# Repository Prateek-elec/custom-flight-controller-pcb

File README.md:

# Custom Drone Flight Controller PCB (KiCad)

A custom-designed drone flight controller PCB built for UAV / robotics applications.
This repository contains schematic + PCB layout designed in **KiCad**, along with documentation and renders.

---

## 🔥 Highlights
- Custom Flight Controller PCB (compact layout)
- Designed for UAV multirotor / robotics use cases
- Includes power regulation, sensor interfaces, and IO headers
- Designed for debugging + expandability

---

## 🧩 Major Blocks (Hardware Architecture)
### ✅ MCU / Processing
- STM32-based microcontroller (flight control core)
- Clocking + reset/boot support

### ✅ Sensors
- IMU interface for attitude estimation (gyro + accel)
- Additional I2C/SPI expansion for future sensors

### ✅ Power System
- Multiple regulated rails for clean operation
- USB/VBUS support
- Protection + filtering for stable power delivery

### ✅ IO / Connectivity
- Motor/ESC outputs (PWM)
- UART ports for telemetry / GPS / RC
- I2C / SPI headers for peripherals
- Status LEDs for debugging/health indication

---

## 🖼️ PCB Preview

### 3D View

### Schematic

---

## 📂 Repository Structure
- `hardware/kicad/` → KiCad source project files
- `docs/images/` → PCB renders & schematic snapshots
- `fabrication/` → Gerbers, drill files, BOM, pick & place
- `firmware/` → Placeholder for future flight firmware integration

---

## 🛠️ Tools Used
- KiCad (Schematic + PCB + 3D viewer)
- Standard PCB manufacturing flow (Gerber + drill export)

---

## ✅ Project Status
- [x] Schematic completed
- [x] PCB layout completed
- [ ] Full firmware integration (planned)
- [ ] Flight testing & tuning (planned / in-progress)

---

## ⚡ Notes
This is a custom hardware project made for learning, experimentation and UAV development.
You can reuse the structure for educational purposes.

---

## 📌 Author
**Prateek Sarkar**  
UAV Systems | Embedded | PCB Design | Robotics

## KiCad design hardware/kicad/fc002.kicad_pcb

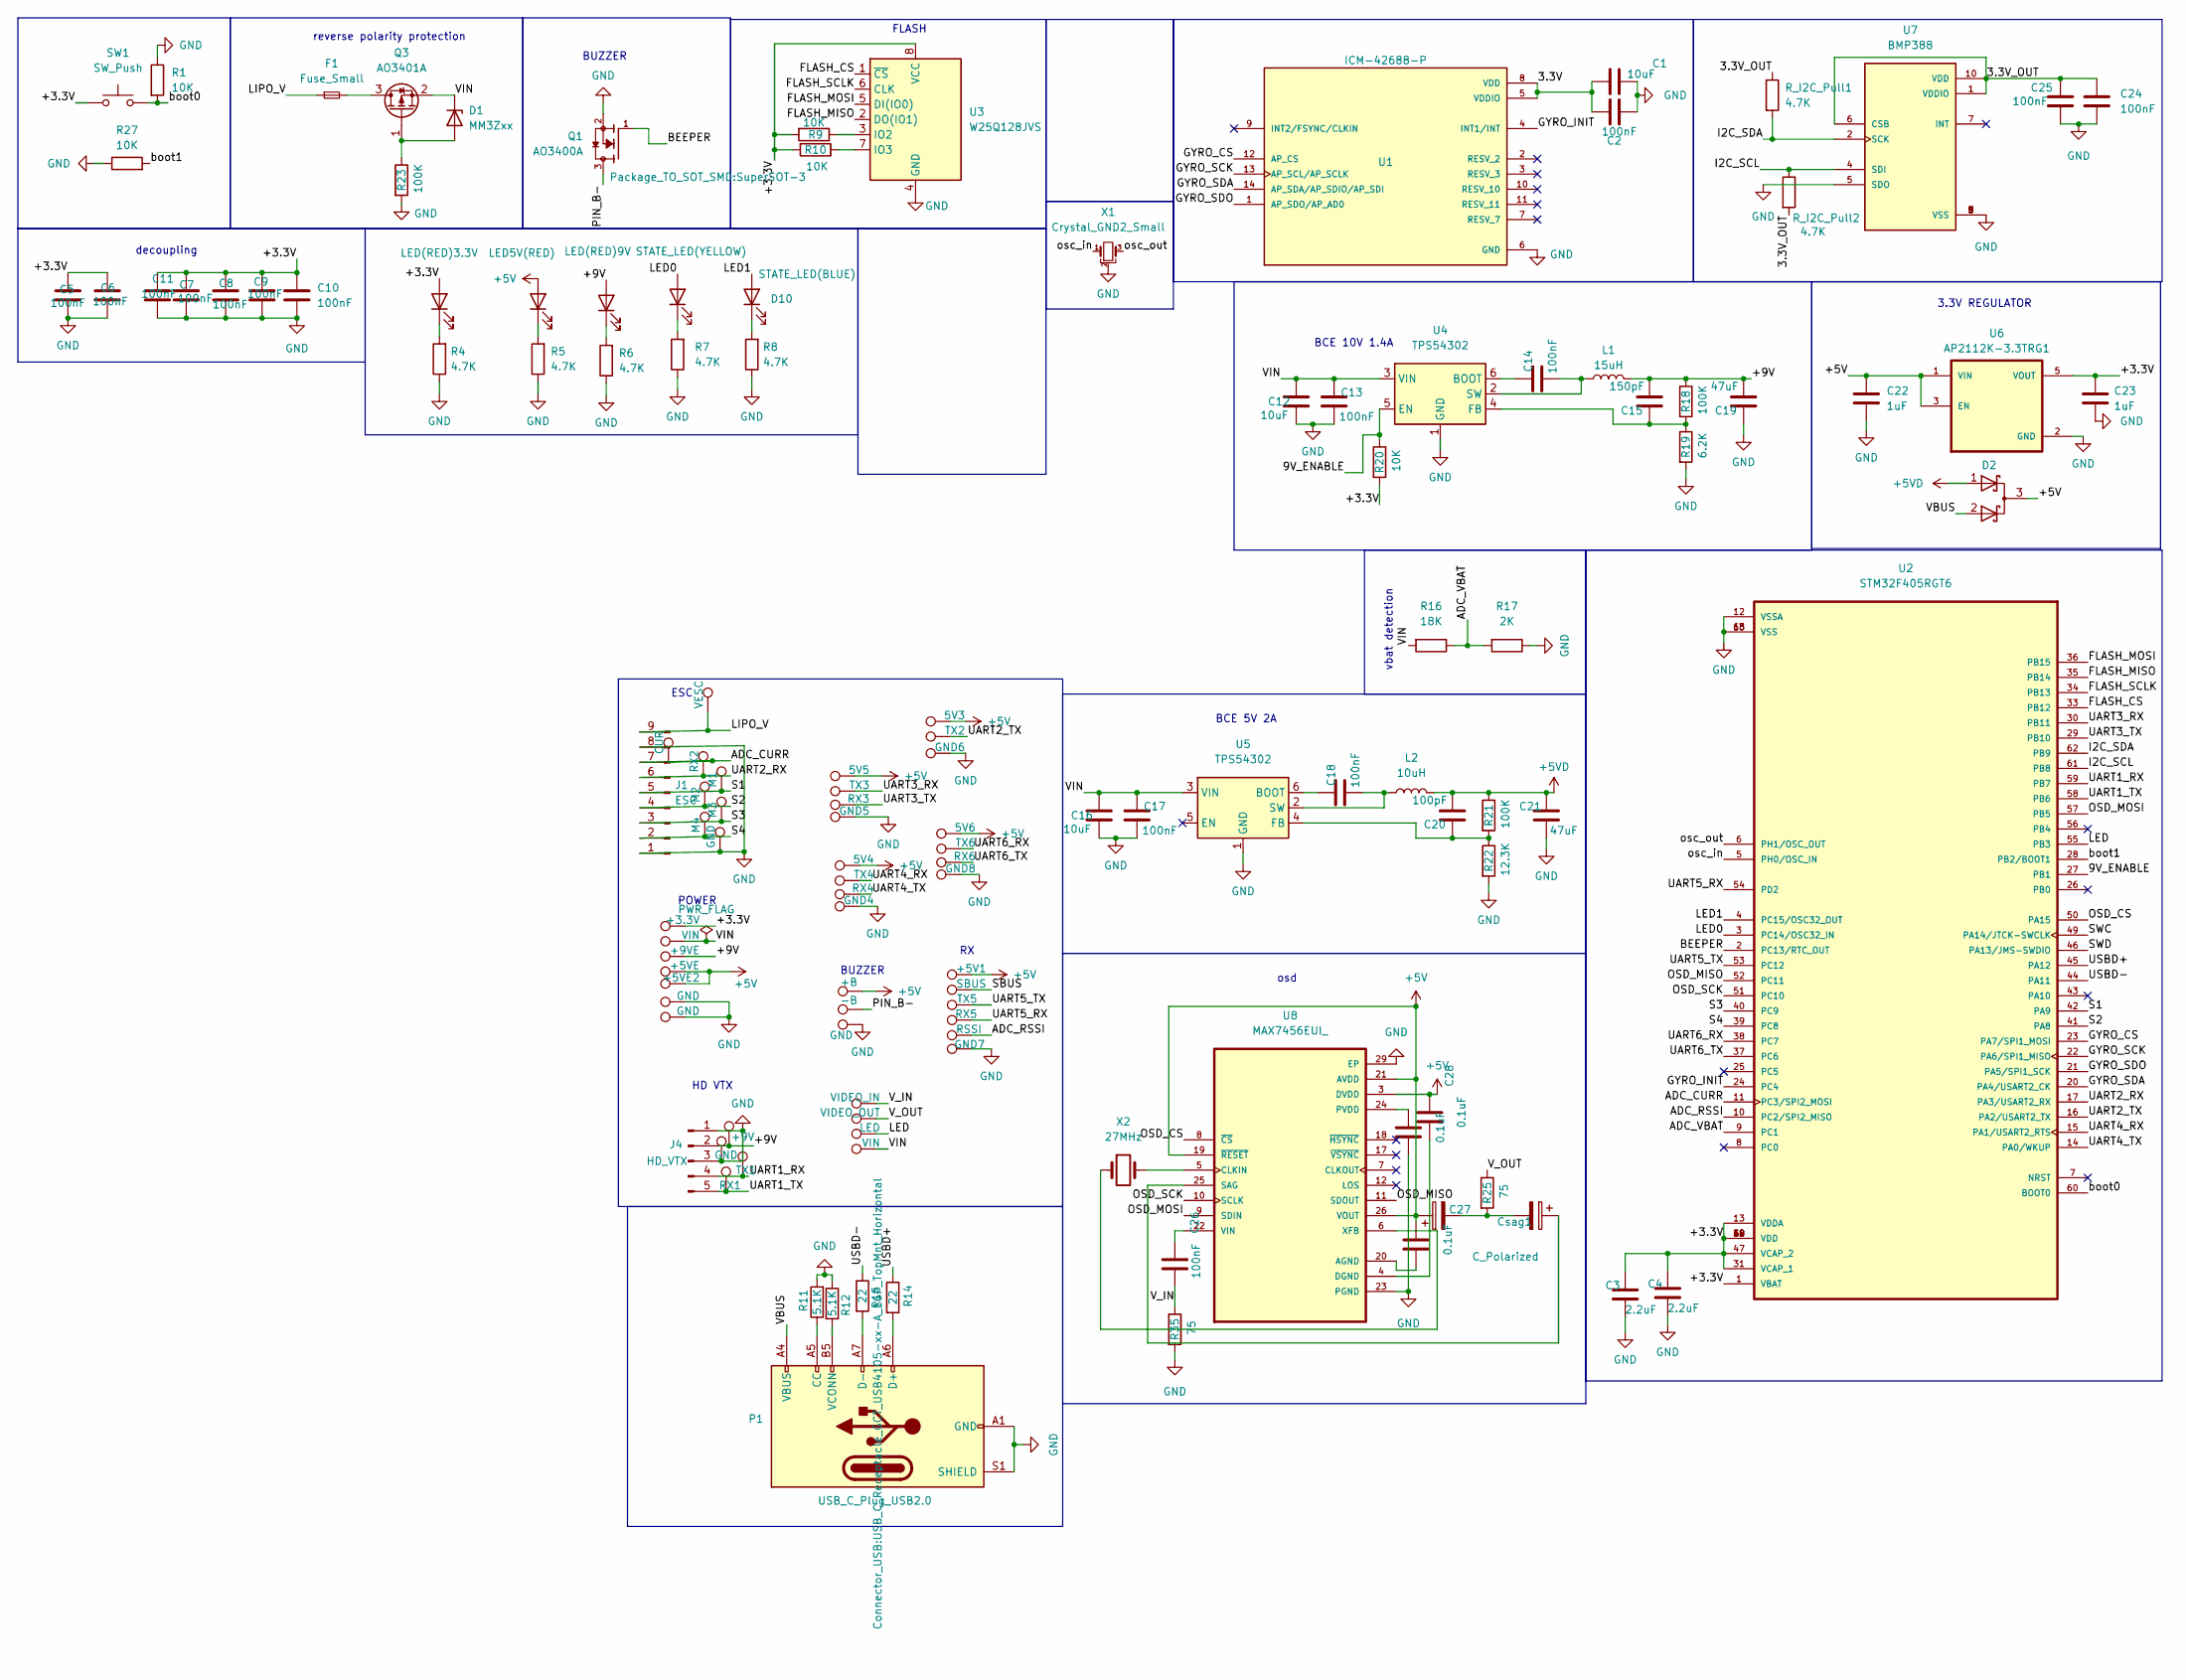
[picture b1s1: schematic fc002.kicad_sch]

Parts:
C1: 10uF; C_0402_1005Metric
C2, C5, C6, C7, C8, C9, C10, C11, C24, C25, C26: 100nF; C_0402_1005Metric
C3, C4: 2.2uF; C_0402_1005Metric
C12, C16: 10uF; C_1206_3216Metric
C13, C14: 100nF; C_0201_0603Metric
C15: 150pF; C_0603_1608Metric
C17, C18: 100nF; C_0603_1608Metric
C19, C21: 47uF; C_1206_3216Metric
C20: 100pF; C_0603_1608Metric
C22, C23: 1uF; C_0402_1005Metric
C27: C_Polarized; C_0603_1608Metric
C28: 0.1uF; C_0603_1608Metric
C_IMU_100n4, C_IMU_100n5: 0.1uF; C_0402_1005Metric
Csag1: C_Polarized; C_0603_1608Metric
D1: MM3Zxx; D_SOD-323F
D2: D_Schottky_Dual_CommonCathode_AAK_Parallel; D_0201_0603Metric
D10: STATE_LED(BLUE); LED_0201_0603Metric
D11: STATE_LED(YELLOW); LED_0201_0603Metric
D12: LED(RED)9V; LED_0201_0603Metric
D13: LED5V(RED); LED_0201_0603Metric
D14: LED(RED)3.3V; LED_0201_0603Metric
F1: Fuse_Small; Fuse_1206_3216Metric
J1: ESC; JST_GH_SM09B-GHS-TB_1x09-1MP_P1.25mm_Horizontal
J4: HD_VTX; JST_GH_SM05B-GHS-TB_1x05-1MP_P1.25mm_Horizontal
L1: 15uH; L_6.3x6.3_H3
L2: 10uH; L_6.3x6.3_H3
P1: USB_C_Plug_USB2.0; USB_C_Receptacle_GCT_USB4105-xx-A_16P_TopMnt_Horizontal
Q1: AO3400A; SuperSOT-3
Q3: AO3401A; SOT-23
R1, R9, R10, R20, R27: 10K; R_0402_1005Metric
R4, R5, R6, R7, R8: 4.7K; R_0402_1005Metric
R11, R12: 5.1K; R_0402_1005Metric
R14, R15: 22; R_0402_1005Metric
R16: 18K; R_0402_1005Metric
R17: 2K; R_0402_1005Metric
R18, R21, R23: 100K; R_0402_1005Metric
R19: 6.2K; R_0402_1005Metric
R22: 12.3K; R_0402_1005Metric
R25, R35: 75; R_0402_1005Metric
R_I2C_Pull1, R_I2C_Pull2: 4.7K; R_0402_1005Metric
SW1: SW_Push; SW_SPST_TS-1088-xR020
TP1: +9V; TestPoint_Pad_1.0x1.0mm
TP2: TX1; TestPoint_Pad_1.0x1.0mm
TP3: RX1; TestPoint_Pad_1.0x1.0mm
TP4, TP6, TP26, TP32, TP33: GND; TestPoint_Pad_1.0x1.0mm
TP5: -B; TestPoint_Pad_1.0x1.0mm
TP7: +5V1; TestPoint_Pad_1.0x1.0mm
TP8: SBUS; TestPoint_Pad_1.0x1.0mm
TP9: TX5; TestPoint_Pad_1.0x1.0mm
TP10: RX5; TestPoint_Pad_1.0x1.0mm
TP11: RSSI; TestPoint_Pad_1.0x1.0mm
TP12: GND7; TestPoint_Pad_1.0x1.0mm
TP15: VIDEO_IN; TestPoint_Pad_1.0x1.0mm
TP16: VIDEO_OUT; TestPoint_Pad_1.0x1.0mm
TP17: LED; TestPoint_Pad_1.0x1.0mm
TP18, TP28: VIN; TestPoint_Pad_1.0x1.0mm
TP19: VESC; TestPoint_Pad_1.0x1.0mm
TP20: CUR; TestPoint_Pad_1.0x1.0mm
TP21: RX2; TestPoint_Pad_1.0x1.0mm
TP22: M1; TestPoint_Pad_1.0x1.0mm
TP23: M2; TestPoint_Pad_1.0x1.0mm
TP24: M3; TestPoint_Pad_1.0x1.0mm
TP25: M4; TestPoint_Pad_1.0x1.0mm
TP27: +3.3V; TestPoint_Pad_1.0x1.0mm
TP29: +9VE; TestPoint_Pad_1.0x1.0mm
TP30: +5VE; TestPoint_Pad_1.0x1.0mm
TP31: +5VE2; TestPoint_Pad_1.0x1.0mm
TP34: 5V5; TestPoint_Pad_1.0x1.0mm
TP35: TX3; TestPoint_Pad_1.0x1.0mm
TP36: RX3; TestPoint_Pad_1.0x1.0mm
TP37: GND5; TestPoint_Pad_1.0x1.0mm
TP38: 5V4; TestPoint_Pad_1.0x1.0mm
TP39: TX4; TestPoint_Pad_1.0x1.0mm
TP40: RX4; TestPoint_Pad_1.0x1.0mm
TP41: GND4; TestPoint_Pad_1.0x1.0mm
TP42: 5V3; TestPoint_Pad_1.0x1.0mm
TP43: TX2; TestPoint_Pad_1.0x1.0mm
TP44: GND6; TestPoint_Pad_1.0x1.0mm
TP45: 5V6; TestPoint_Pad_1.0x1.0mm
TP46: TX6; TestPoint_Pad_1.0x1.0mm
TP47: RX6; TestPoint_Pad_1.0x1.0mm
TP48: GND8; TestPoint_Pad_1.0x1.0mm
TP49: +B; TestPoint_Pad_1.0x1.0mm
U1: ICM-42688-P; LGA-14_3x2.5mm_P0.5mm_LayoutBorder3x4y; PARTREV 1.2
U2: STM32F405RGT6; LQFP-64-1EP_10x10mm_P0.5mm_EP6.5x6.5mm; PARTREV LTR
U3: W25Q128JVS; SOIC-8_5.3x5.3mm_P1.27mm
U4, U5: TPS54302; SOT-23-6
U6: AP2112K-3.3TRG1; SOT-23-5; PARTREV 2-2
U7: BMP388; ST_HLGA-10_2x2mm_P0.5mm_LayoutBorder3x2y; PARTREV 1.1
U8: MAX7456EUI_; TSSOP-28_4.4x9.7mm_P0.65mm
X1: Crystal_GND2_Small; Resonator_SMD_Murata_CSTxExxV-3Pin_3.0x1.1mm
X2: 27MHz; Crystal_SMD_SeikoEpson_FA238-4Pin_3.2x2.5mm

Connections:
+5V: C22.1, C27.1, C28.2, C_IMU_100n5.2, D2.3 (A), D13.2 (A), TP7.1, TP30.1, TP31.1, TP34.1, TP38.1, TP42.1, TP45.1, TP49.1, U6.1 (VIN), U6.3 (EN), U8.3 (DVDD), U8.19 (~RESET), U8.21 (AVDD), U8.26 (VOUT)
+5VD: C20.2, C21.2, D2.1 (K), L2.2, R21.1
/3.3V: C1.1, C2.1, U1.5 (VDDIO), U1.8 (VDD)
/3.3V_OUT: C24.1, C25.1, R_I2C_Pull1.1, R_I2C_Pull2.2, U7.1 (VDDIO), U7.6 (CSB), U7.10 (VDD)
/9V_ENABLE: R20.1, U2.27 (PB1), U4.5 (EN)
/+3.3V: C3.2, C4.2, C5.1, C6.1, C7.1, C8.1, C9.1, C10.1, C11.1, C23.1, D14.2 (A), R9.2, R10.2, R20.2, SW1.1, TP27.1, U2.1 (VBAT), U2.13 (VDDA), U2.19 (VDD), U2.31 (VCAP_1), U2.32 (VDD), U2.47 (VCAP_2), U2.48 (VDD), U2.64 (VDD), U3.8 (VCC), U6.5 (VOUT)
/+9V: C15.2, C19.2, D12.2 (A), J4.2, L1.2, R18.1, TP1.1, TP29.1
/ADC_CURR: J1.7, TP20.1, U2.11 (PC3/SPI2_MOSI)
/ADC_RSSI: TP11.1, U2.10 (PC2/SPI2_MISO)
/ADC_VBAT: R16.1, R17.2, U2.9 (PC1)
/BEEPER: Q1.1, U2.2 (PC13/RTC_OUT)
/FLASH_CS: U2.33 (PB12), U3.1 (~CS)
/FLASH_MISO: U2.35 (PB14), U3.2 (DO(IO1))
/FLASH_MOSI: U2.36 (PB15), U3.5 (DI(IO0))
/FLASH_SCLK: U2.34 (PB13), U3.6 (CLK)
/GYRO_CS: U1.12 (AP_CS), U2.23 (PA7/SPI1_MOSI)
/GYRO_INIT: U1.4 (INT1/INT), U2.24 (PC4)
/GYRO_SCK: U1.13 (AP_SCL/AP_SCLK), U2.22 (PA6/SPI1_MISO)
/GYRO_SDA: U1.14 (AP_SDA/AP_SDIO/AP_SDI), U2.20 (PA4/USART2_CK)
/GYRO_SDO: U1.1 (AP_SDO/AP_AD0), U2.21 (PA5/SPI1_SCK)
/I2C_SCL: R_I2C_Pull2.1, U2.61 (PB8), U7.4 (SDI)
/I2C_SDA: R_I2C_Pull1.2, U2.62 (PB9), U7.2 (SCK)
/LED: TP17.1, U2.55 (PB3)
/LED0: D11.2 (A), U2.3 (PC14/OSC32_IN)
/LED1: D10.2 (A), U2.4 (PC15/OSC32_OUT)
/LIPO_V: F1.1, J1.9, TP19.1
/OSD_CS: U2.50 (PA15), U8.8 (~CS)
/OSD_MISO: U2.52 (PC11), U8.11 (SDOUT)
/OSD_MOSI: U2.57 (PB5), U8.9 (SDIN)
/OSD_SCK: U2.51 (PC10), U8.10 (SCLK)
/PIN_B-: Q1.3, TP5.1
/S1: J1.5, TP22.1, U2.42 (PA9)
/S2: J1.4, TP23.1, U2.41 (PA8)
/S3: J1.3, TP24.1, U2.40 (PC9)
/S4: J1.2, TP25.1, U2.39 (PC8)
/SWC: U2.49 (PA14/JTCK-SWCLK)
/SWD: U2.46 (PA13/JMS-SWDIO)
/UART1_RX: J4.4, TP2.1, U2.59 (PB7)
/UART1_TX: J4.5, TP3.1, U2.58 (PB6)
/UART2_RX: J1.6, TP21.1, U2.17 (PA3/USART2_RX)
/UART2_TX: TP43.1, U2.16 (PA2/USART2_TX)
/UART3_RX: TP35.1, U2.30 (PB11)
/UART3_TX: TP36.1, U2.29 (PB10)
/UART4_RX: TP39.1, U2.15 (PA1/USART2_RTS)
/UART4_TX: TP40.1, U2.14 (PA0/WKUP)
/UART5_RX: TP10.1, U2.54 (PD2)
/UART5_TX: TP9.1, U2.53 (PC12)
/UART6_RX: TP46.1, U2.38 (PC7)
/UART6_TX: TP47.1, U2.37 (PC6)
/USBD+: R14.1, U2.45 (PA12)
/USBD-: R15.1, U2.44 (PA11)
/VBUS: D2.2 (K), P1.A4 (VBUS), P1.A9 (VBUS), P1.B4 (VBUS), P1.B9 (VBUS)
/VIN: C12.1, C13.1, C16.1, C17.1, D1.1 (K), Q3.2 (S), R16.2, TP18.1, TP28.1, U4.3 (VIN), U5.3 (VIN)
/V_IN: C26.1, R35.1, TP15.1
/V_OUT: R25.1, TP16.1
/boot0: R1.2, SW1.2, U2.60 (BOOT0)
/boot1: R27.2, U2.28 (PB2/BOOT1)
/osc_in: U2.5 (PH0/OSC_IN), X1.1
/osc_out: U2.6 (PH1/OSC_OUT), X1.3
GND: C1.2, C2.2, C3.1, C4.1, C5.2, C6.2, C7.2, C8.2, C9.2, C10.2, C11.2, C12.2, C13.2, C16.2, C17.2, C19.1, C21.1, C22.2, C23.2, C24.2, C25.2, C_IMU_100n4.1, J1.1, J1.8, J4.1, J4.3, P1.A1 (GND), P1.A12 (GND), P1.B1 (GND), P1.B12 (GND), P1.S1 (SHIELD), Q1.2, R1.1, R4.1, R5.1, R6.1, R7.1, R8.1, R11.2, R12.1, R17.1, R19.2, R22.2, R23.2, R27.1, R35.2, TP4.1, TP6.1, TP12.1, TP26.1, TP32.1, TP33.1, TP37.1, TP41.1, TP44.1, TP48.1, U1.6 (GND), U2.12 (VSSA), U2.18 (VSS), U2.63 (VSS), U3.4 (GND), U4.1 (GND), U5.1 (GND), U6.2 (GND), U7.3 (VSS), U7.5 (SDO), U7.8 (VSS), U7.9 (VSS), U8.23 (PGND), U8.29 (EP), X1.2
unnamed: C27.2, Csag1.2, R25.2
unnamed: D1.2 (A), Q3.1 (G), R23.1
unnamed: D10.1 (K), R8.2
unnamed: D11.1 (K), R7.2
unnamed: D12.1 (K), R6.2
unnamed: D13.1 (K), R5.2
unnamed: D14.1 (K), R4.2
unnamed: P1.A5 (CC), R11.1
unnamed: P1.A6 (D+), R14.2
unnamed: P1.A7 (D-), R15.2
unnamed: P1.B5 (VCONN), R12.2
unnamed: F1.2, Q3.3 (D)
unnamed: R9.1, U3.3 (IO2)
unnamed: R10.1, U3.7 (IO3)
unnamed: C14.1, U4.6 (BOOT)
unnamed: C15.1, R18.2, R19.1, U4.4 (FB)
unnamed: C14.2, L1.1, U4.2 (SW)
unnamed: C18.1, U5.6 (BOOT)
unnamed: C20.1, R21.2, R22.1, U5.4 (FB)
unnamed: C18.2, L2.1, U5.2 (SW)
unnamed: C_IMU_100n5.1, U8.20 (AGND)
unnamed: U8.5 (CLKIN), X2.2
unnamed: C28.1, U8.4 (DGND)
unnamed: C_IMU_100n4.2, U8.24 (PVDD)
unnamed: Csag1.1, U8.25 (SAG)
unnamed: C26.2, U8.22 (VIN)
unnamed: U8.6 (XFB), X2.1

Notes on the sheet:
HD VTX
3.3V REGULATOR
BUZZER
BCE 5V 2A
reverse polarity protection
vbat detection
osd
decoupling
POWER
ESC
BCE 10V 1.4A
FLASH

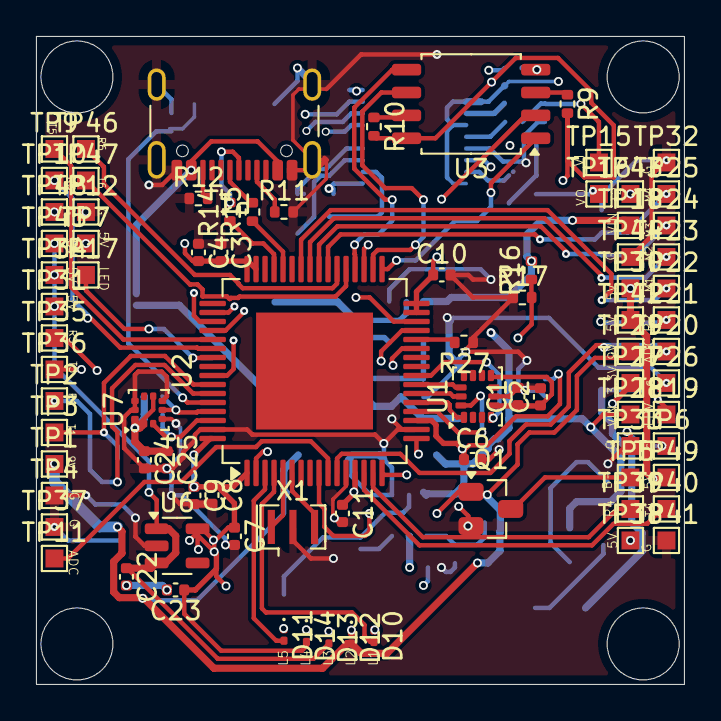
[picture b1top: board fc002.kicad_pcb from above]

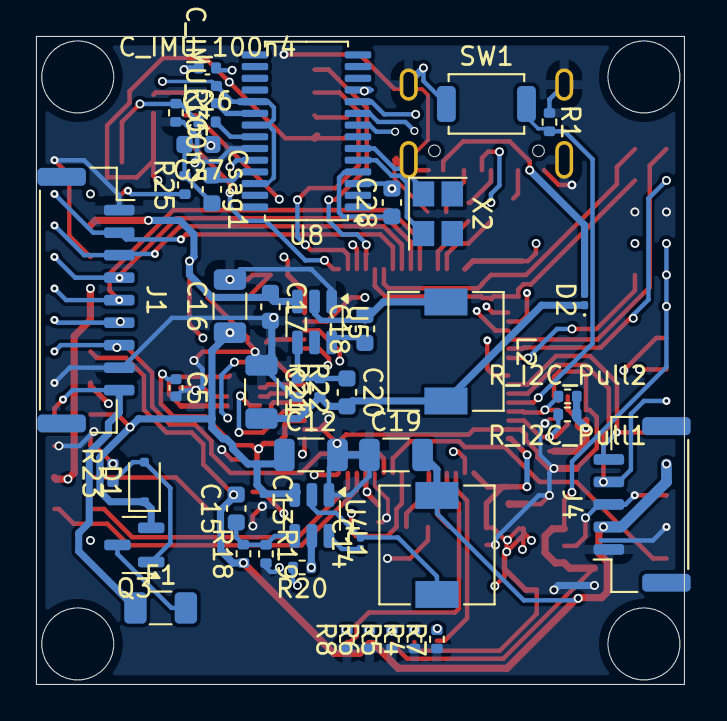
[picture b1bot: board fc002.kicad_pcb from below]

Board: 4 copper layers, 36.0 x 36.0 mm, 128 parts (46 on the bottom side), 85 nets.
